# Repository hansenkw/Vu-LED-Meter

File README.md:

# Vu-LED-Meter
This is a decorative LED that shines based on the audio input through the 3.5mm audio jack connector. The design is a 2-layer printed circuit board (PCB) based on Great Scott Vu LED Meter (https://www.instructables.com/Make-Your-Own-LED-Sign-VU-Meter/) with few modifications as seen below. 
  - Changed through-hole (THT) to surface-mounted (SMD) components, allowing space-effiecient design.
  - Designed a 12V-5V DCDC buck converter circuitry instead of using off the shelf module, integrated it with the rest of the circuitry into one PCB.
  - Utilized six (instead of seven) audio voltage references with each associated with a single row of LEDs.
  - Addeed current-limiting resistors to reduce current consumption.

# Overview

# Schematic Design

# Layout

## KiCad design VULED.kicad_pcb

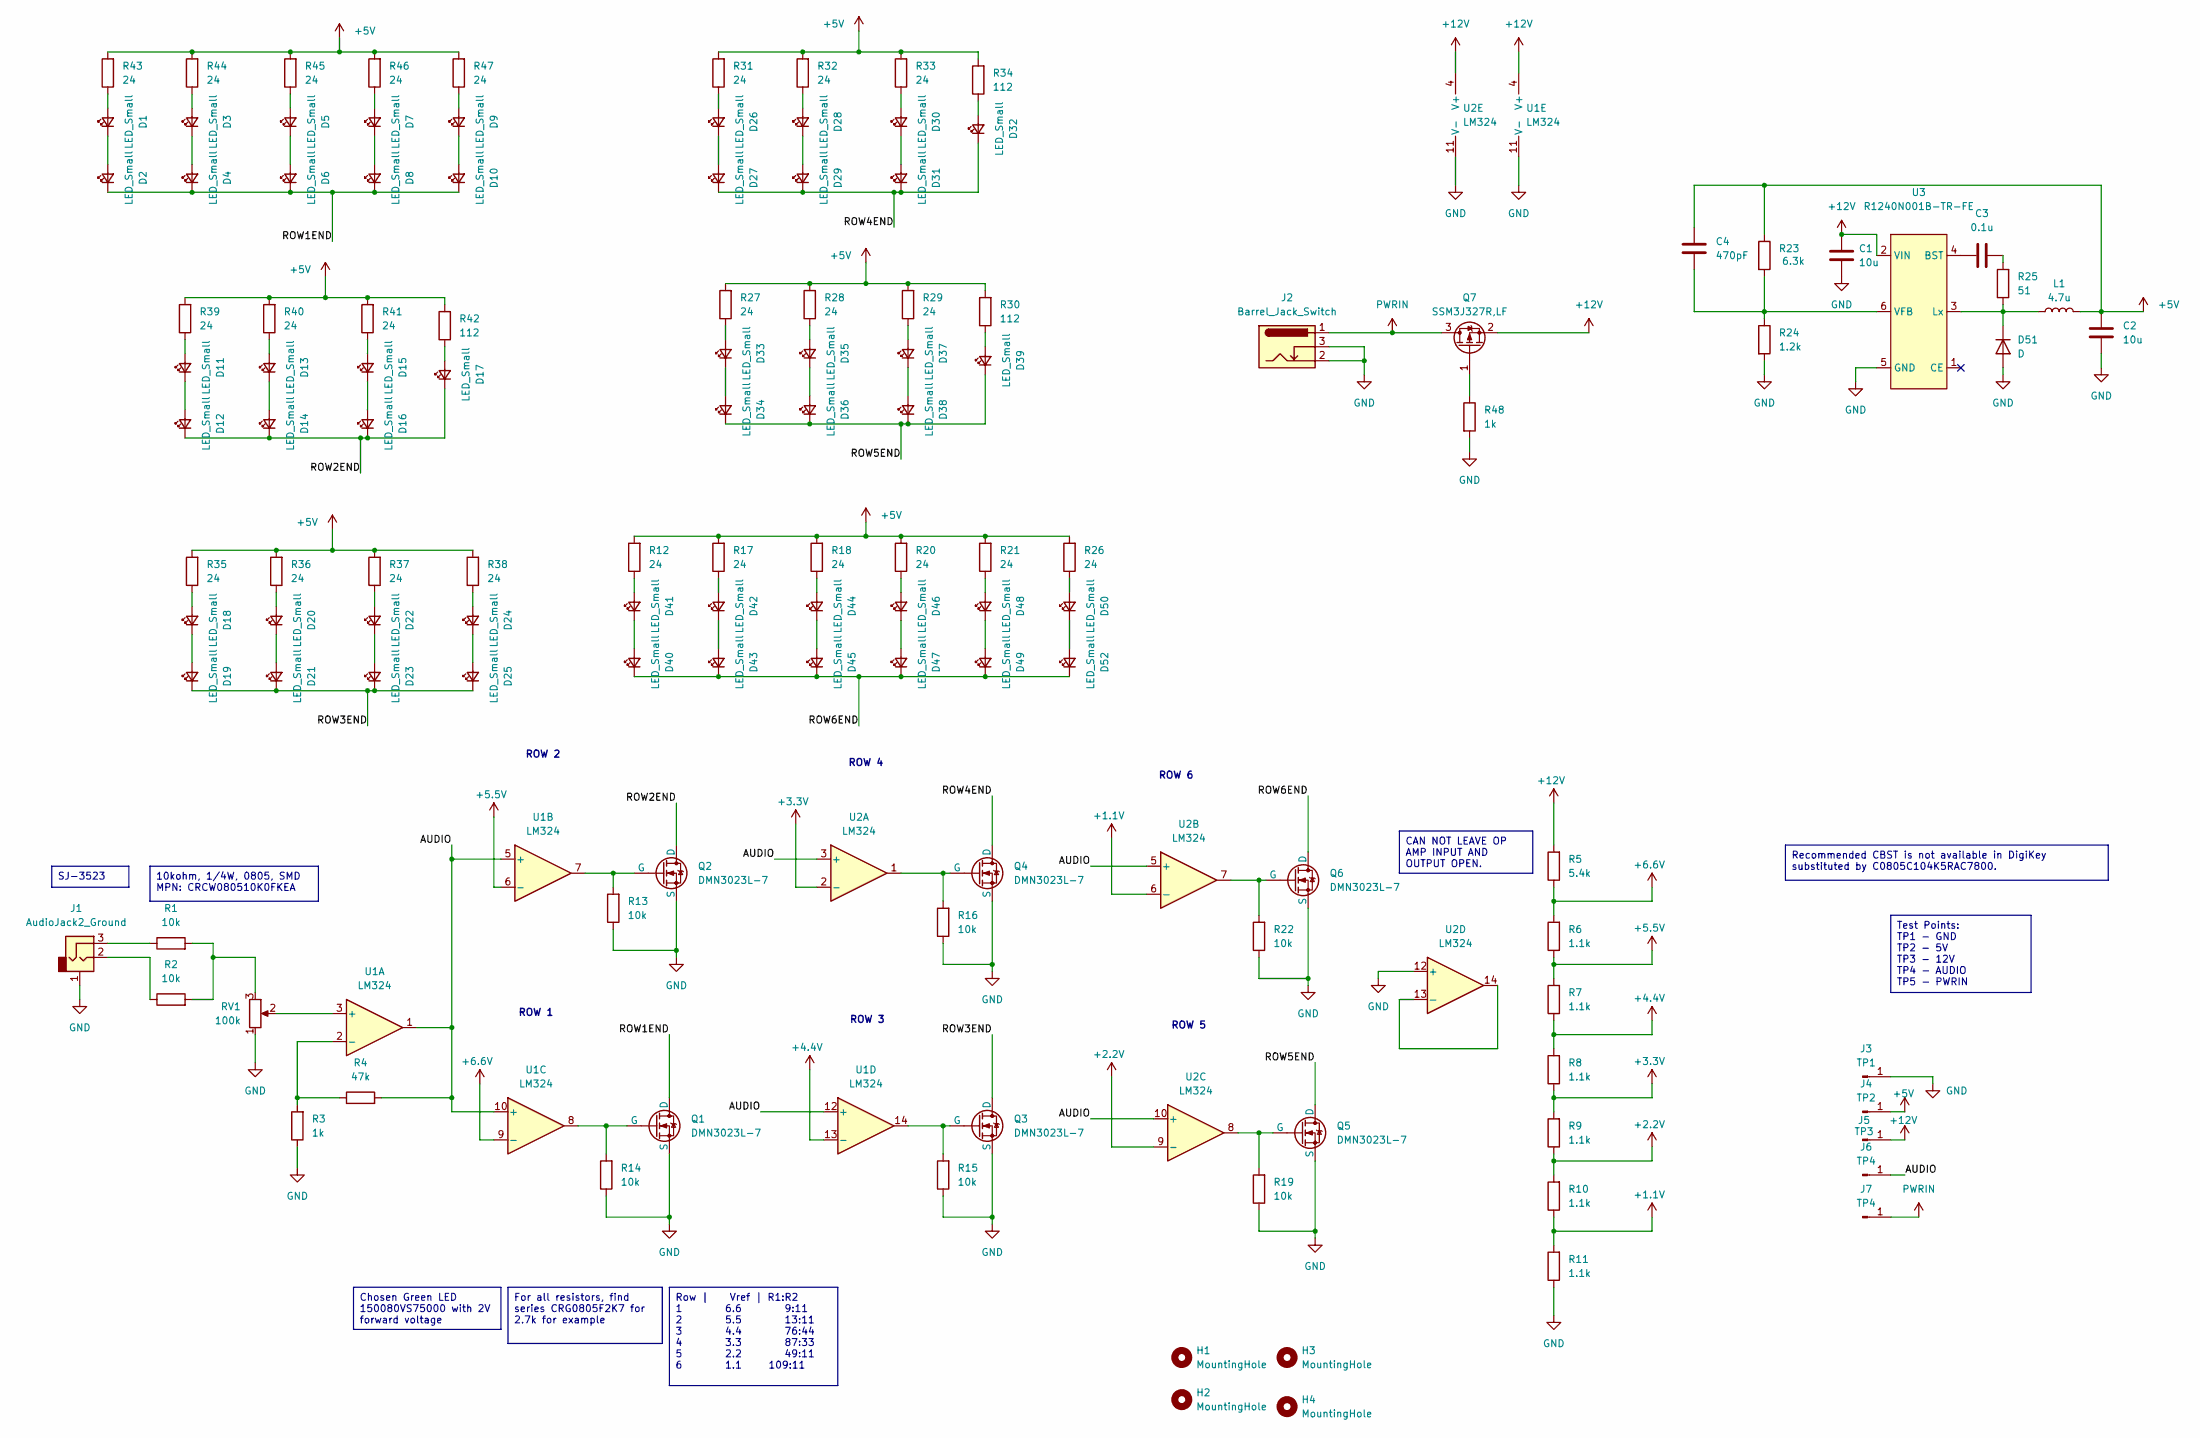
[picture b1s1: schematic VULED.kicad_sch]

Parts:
C1: 10u; KTS500B106M55N0T00
C2: 10u; GRM31CR71E106KA12L
C3: 0.1u; C0805C104K5RACTU
C4: 470pF; C_0201_0603Metric
D1, D2, D3, D4, D5, D6, D7, D8, D9, D10, D11, D12, D13, D14, D15, D16, D17, D18, D19, D20, D21, D22, D23, D24, D25, D26, D27, D28, D29, D30, D31, D32, D33, D34, D35, D36, D37, D38, D39, D40, D41, D42, D43, D44, D45, D46, D47, D48, D49, D50, D52: LED_Small; 150080VS75000-WL-SMCW_0805
D51: D; CMS11
H1, H2, H3, H4: MountingHole; M3-Mounting Holes
J1: AudioJack2_Ground; STX-3000_KYC
J2: Barrel_Jack_Switch; EJ508A
J3: TP1; PH1_01_UA
J4: TP2; PH1_01_UA
J5: TP3; PH1_01_UA
J6, J7: TP4; PH1_01_UA
L1: 4.7u; IND_SLF7045T-4R7M2R0-PF
Q1, Q2, Q3, Q4, Q5, Q6: DMN3023L-7; DMN3023L_7
Q7: SSM3J327R,LF; SSM3J327R-LF
R1, R2: 10k; RESC2012X50N
R3, R48: 1k; RES0805_CRG_TYCO_TYC
R4: 47k; RES0805_CRG_TYCO_TYC
R5: 5.4k; RES0805_CRG_TYCO_TYC
R6, R7, R8, R9, R10, R11: 1.1k; RES0805_CRG_TYCO_TYC
R12, R17, R18, R20, R21, R26, R27, R28, R29, R31, R32, R33, R35, R36, R37, R38, R39, R40, R41, R43, R44, R45, R46, R47: 24; CPF0603B24RE1
R13, R14, R15, R16, R19, R22: 10k; RES0805_CRG_TYCO_TYC
R23: 6.3k; RES0805_CRG_TYCO_TYC
R24: 1.2k; RES0805_CRG_TYCO_TYC
R25: 51; RC0805FR-0751RL
R30, R34, R42: 112; RES0805_CRG_TYCO_TYC
RV1: 100k; POT_PTA3043_BRN
U1: LM324; LM324-D14-M
U2: LM324
U3: R1240N001B-TR-FE; SOT-23-6W_PE-SOT23-6W-0512_NMD

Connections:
+1.1V: R10.1, R11.2, U2.6 (-)
+2.2V: R9.1, R10.2, U2.9 (-)
+3.3V: R8.1, R9.2, U2.2 (-)
+4.4V: R7.1, R8.2, U1.13 (-)
+5.5V: R6.1, R7.2, U1.6 (-)
+5V: C2.1, C4.1, J4.1, L1.2, R12.2, R17.2, R18.2, R20.2, R21.2, R23.1, R26.2, R27.2, R28.2, R29.2, R30.2, R31.2, R32.2, R33.2, R34.2, R35.2, R36.2, R37.2, R38.2, R39.2, R40.2, R41.2, R42.2, R43.2, R44.2, R45.2, R46.2, R47.2
+6.6V: R5.1, R6.2, U1.9 (-)
+12V: C1.1, J5.1, Q7.2 (S), R5.2, U1.4 (V+), U2.4 (V+), U3.2 (VIN)
/AUDIO: J6.1, R4.2, U1.1, U1.5 (+), U1.10 (+), U1.12 (+), U2.3 (+), U2.5 (+), U2.10 (+)
/ROW1END: D2.1 (K), D4.1 (K), D6.1 (K), D8.1 (K), D10.1 (K), Q1.1 (D)
/ROW2END: D12.1 (K), D14.1 (K), D16.1 (K), D17.1 (K), Q2.1 (D)
/ROW3END: D19.1 (K), D21.1 (K), D23.1 (K), D25.1 (K), Q3.1 (D)
/ROW4END: D27.1 (K), D29.1 (K), D31.1 (K), D32.1 (K), Q4.1 (D)
/ROW5END: D34.1 (K), D36.1 (K), D38.1 (K), D39.1 (K), Q5.1 (D)
/ROW6END: D40.1 (K), D43.1 (K), D45.1 (K), D47.1 (K), D49.1 (K), D52.1 (K), Q6.1 (D)
GND: C1.2, C2.2, D51.2 (A), J1.1, J2.2, J2.3, J3.1, Q1.3 (S), Q2.3 (S), Q3.3 (S), Q4.3 (S), Q5.3 (S), Q6.3 (S), R3.1, R11.1, R13.1, R14.1, R15.1, R16.1, R19.1, R22.1, R24.2, R48.2, RV1.1, U1.11 (V-), U2.11 (V-), U2.12 (+), U3.5 (GND)
unnamed: C3.2, R25.2
unnamed: D1.2 (A), R43.1
unnamed: D1.1 (K), D2.2 (A)
unnamed: D3.2 (A), R44.1
unnamed: D3.1 (K), D4.2 (A)
unnamed: D5.2 (A), R45.1
unnamed: D5.1 (K), D6.2 (A)
unnamed: D7.2 (A), R46.1
unnamed: D7.1 (K), D8.2 (A)
unnamed: D9.2 (A), R47.1
unnamed: D9.1 (K), D10.2 (A)
unnamed: D11.2 (A), R39.1
unnamed: D11.1 (K), D12.2 (A)
unnamed: D13.2 (A), R40.1
unnamed: D13.1 (K), D14.2 (A)
unnamed: D15.2 (A), R41.1
unnamed: D15.1 (K), D16.2 (A)
unnamed: D17.2 (A), R42.1
unnamed: D18.2 (A), R35.1
unnamed: D18.1 (K), D19.2 (A)
unnamed: D20.2 (A), R36.1
unnamed: D20.1 (K), D21.2 (A)
unnamed: D22.2 (A), R37.1
unnamed: D22.1 (K), D23.2 (A)
unnamed: D24.2 (A), R38.1
unnamed: D24.1 (K), D25.2 (A)
unnamed: D26.2 (A), R31.1
unnamed: D26.1 (K), D27.2 (A)
unnamed: D28.2 (A), R32.1
unnamed: D28.1 (K), D29.2 (A)
unnamed: D30.2 (A), R33.1
unnamed: D30.1 (K), D31.2 (A)
unnamed: D32.2 (A), R34.1
unnamed: D33.2 (A), R27.1
unnamed: D33.1 (K), D34.2 (A)
unnamed: D35.2 (A), R28.1
unnamed: D35.1 (K), D36.2 (A)
unnamed: D37.2 (A), R29.1
unnamed: D37.1 (K), D38.2 (A)
unnamed: D39.2 (A), R30.1
unnamed: D40.2 (A), D41.1 (K)
unnamed: D41.2 (A), R12.1
unnamed: D42.2 (A), R17.1
unnamed: D42.1 (K), D43.2 (A)
unnamed: D44.2 (A), R18.1
unnamed: D44.1 (K), D45.2 (A)
unnamed: D46.2 (A), R20.1
unnamed: D46.1 (K), D47.2 (A)
unnamed: D48.2 (A), R21.1
unnamed: D48.1 (K), D49.2 (A)
unnamed: D50.2 (A), R26.1
unnamed: D50.1 (K), D52.2 (A)
unnamed: D51.1 (K), L1.1, R25.1, U3.3 (Lx)
unnamed: J1.2, R2.1
unnamed: J1.3, R1.1
unnamed: Q1.2 (G), R14.2, U1.8
unnamed: Q2.2 (G), R13.2, U1.7
unnamed: Q3.2 (G), R15.2, U1.14
unnamed: Q4.2 (G), R16.2, U2.1
unnamed: Q5.2 (G), R19.2, U2.8
unnamed: Q6.2 (G), R22.2, U2.7
unnamed: Q7.1 (G), R48.1
unnamed: R1.2, R2.2, RV1.3
unnamed: RV1.2, U1.3 (+)
unnamed: R3.2, R4.1, U1.2 (-)
unnamed: C3.1, U3.4 (BST)
unnamed: C4.2, R23.2, R24.1, U3.6 (VFB)
PWRIN: J2.1, J7.1, Q7.3 (D)

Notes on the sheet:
Row | Vref | R1:R2 1 6.6 9:11 2 5.5 13:11 3 4.4 76:44 4 3.3 87:33 5 2.2 49:11 6 1.1 109:11
SJ-3523
Chosen Green LED 150080VS75000 with 2V forward voltage
Test Points: TP1 - GND TP2 - 5V TP3 - 12V TP4 - AUDIO TP5 - PWRIN
10kohm, 1/4W, 0805, SMD MPN: CRCW080510K0FKEA
For all resistors, find series CRG0805F2K7 for 2.7k for example
CAN NOT LEAVE OP AMP INPUT AND OUTPUT OPEN.
Recommended CBST is not available in DigiKey substituted by C0805C104K5RAC7800.
ROW 2
ROW 3
ROW 5
ROW 1
ROW 4
ROW 6

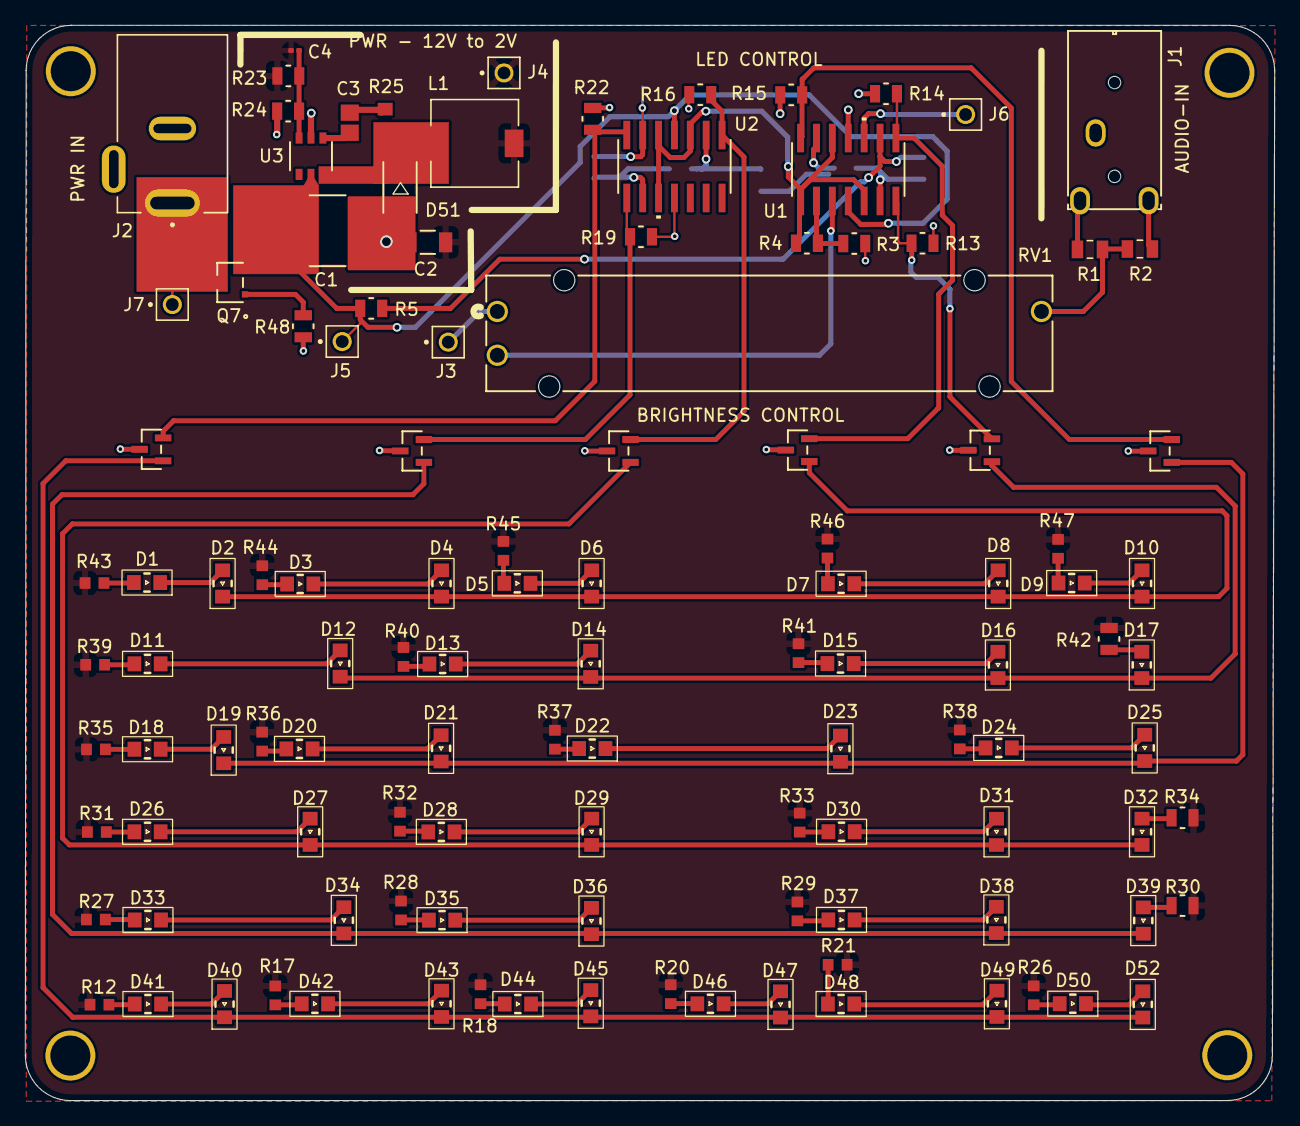
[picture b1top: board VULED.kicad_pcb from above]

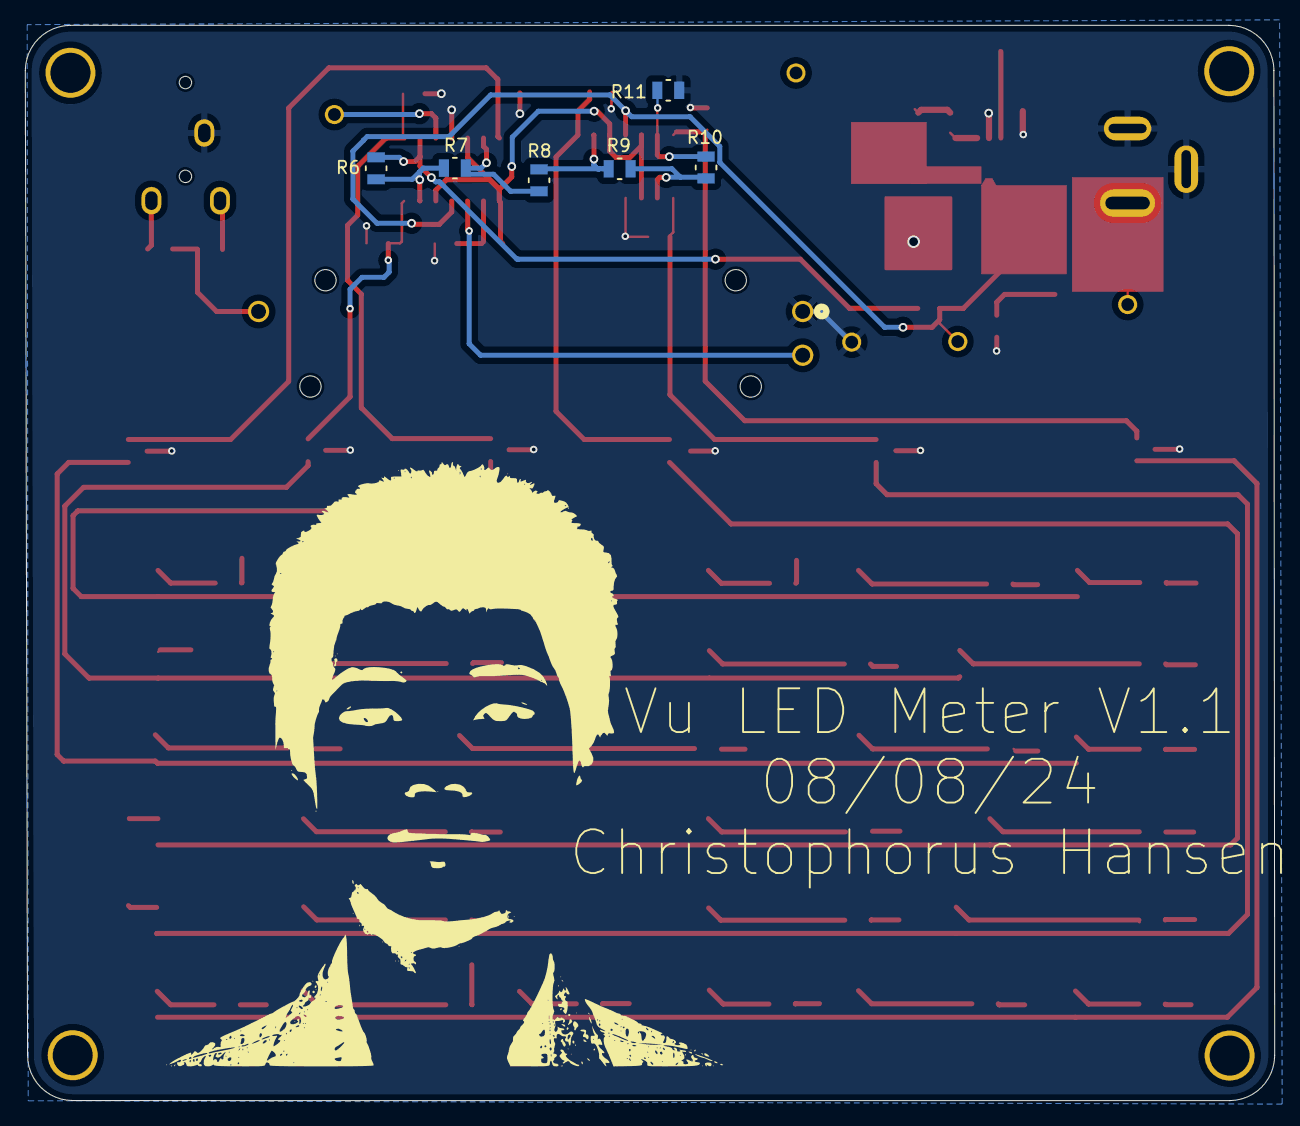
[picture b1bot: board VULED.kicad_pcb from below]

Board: 2 copper layers, 99.9 x 86.0 mm, 127 parts (6 on the bottom side), 84 nets.

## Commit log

2024-08-27 V1.1
    August 27, 2024 commit
